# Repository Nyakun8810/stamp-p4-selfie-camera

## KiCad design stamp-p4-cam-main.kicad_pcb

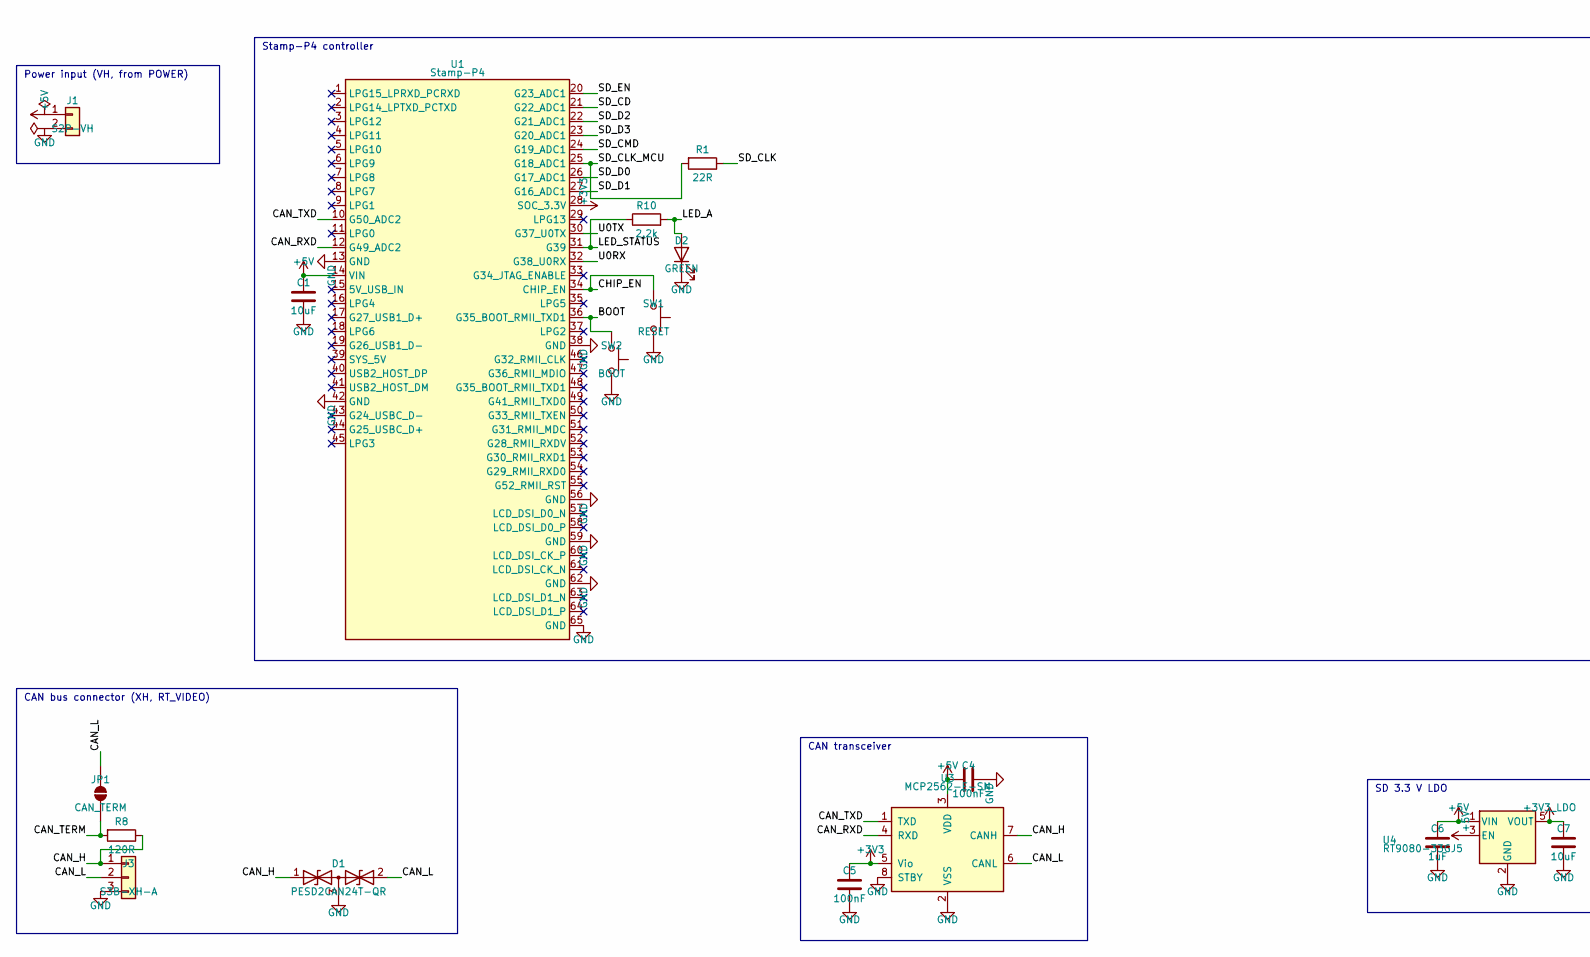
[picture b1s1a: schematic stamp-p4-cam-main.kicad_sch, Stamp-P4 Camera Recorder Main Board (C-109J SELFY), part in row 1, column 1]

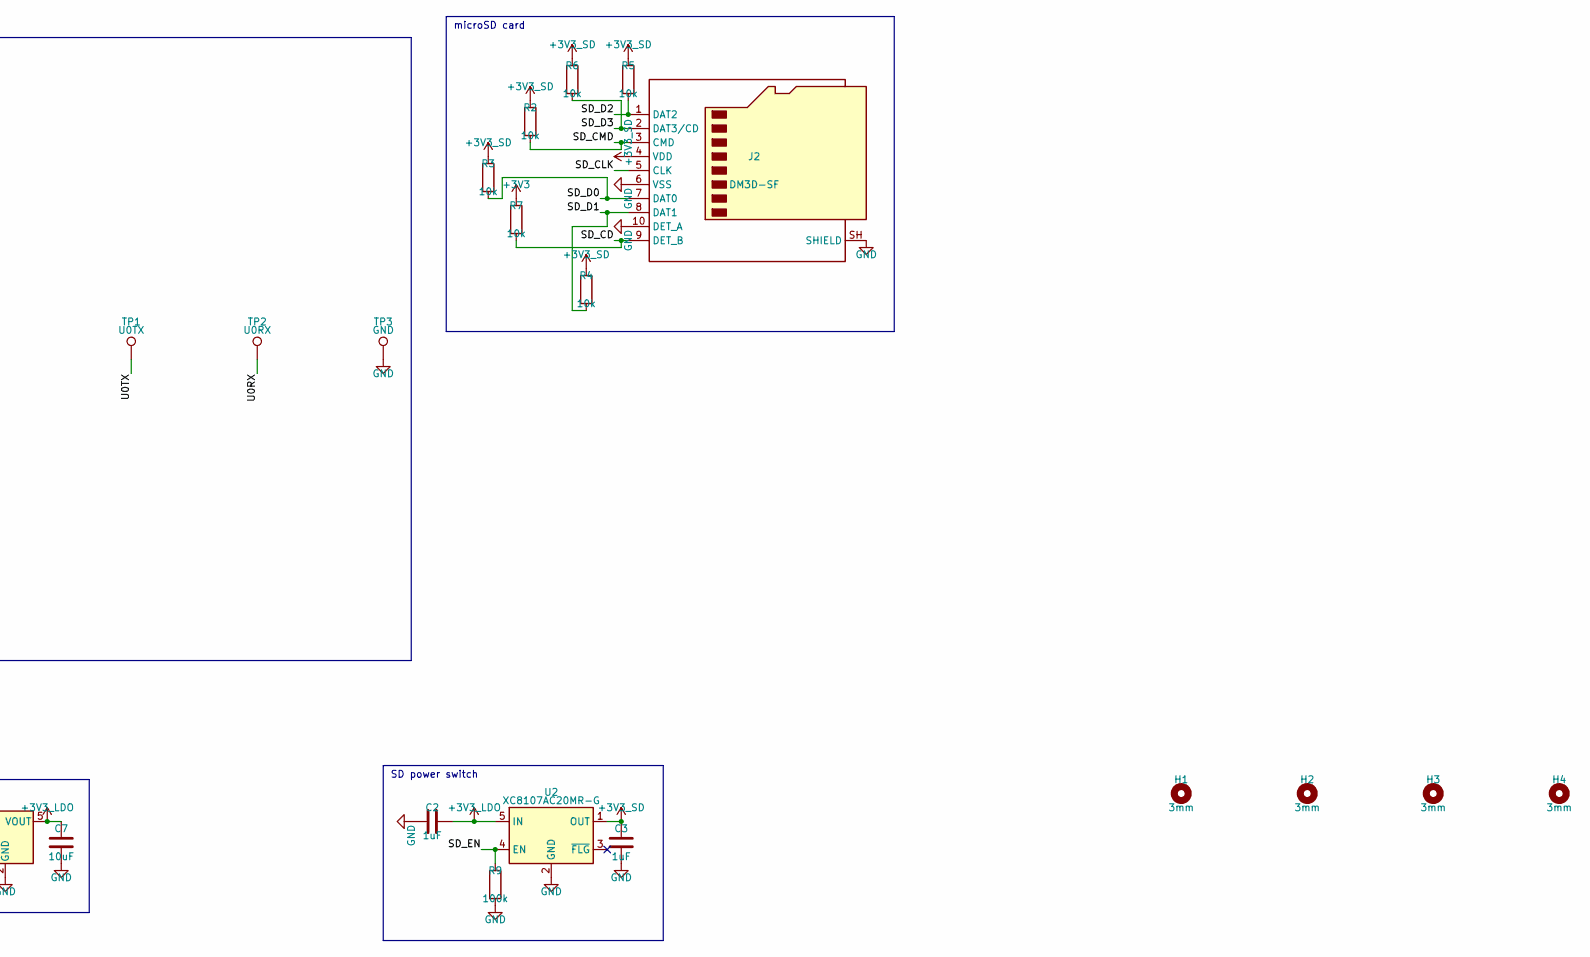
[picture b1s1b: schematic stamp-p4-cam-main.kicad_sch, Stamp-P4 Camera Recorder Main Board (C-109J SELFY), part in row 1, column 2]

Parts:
C1, C7: 10uF; C_0603_1608Metric
C2, C3, C6: 1uF; C_0402_1005Metric
C4, C5: 100nF; C_0402_1005Metric
D1: PESD2CAN24T-QR; SOT-23; MPN PESD2CAN24T-QR
D2: GREEN; LED_0603_1608Metric
H1, H2, H3, H4: 3mm; MountingHole_3mm
J1: S2P-VH; JST_VH_S2P-VH_1x02_P3.96mm_Horizontal; MPN S2P-VH
J2: DM3D-SF; microSD_HC_Hirose_DM3D-SF; MPN DM3D-SF
J3: S3B-XH-A; JST_XH_S3B-XH-A_1x03_P2.50mm_Horizontal; MPN S3B-XH-A
JP1: CAN_TERM; SolderJumper-2_P1.3mm_Open_RoundedPad1.0x1.5mm
R1: 22R; R_0402_1005Metric
R2, R3, R4, R5, R6, R7: 10k; R_0402_1005Metric
R8: 120R; R_0603_1608Metric
R9: 100k; R_0402_1005Metric
R10: 2.2k; R_0402_1005Metric
SW1: RESET; SW_SPST_B3U-1000P
SW2: BOOT; SW_SPST_B3U-1000P
TP1: U0TX; TestPoint_Pad_D1.0mm
TP2: U0RX; TestPoint_Pad_D1.0mm
TP3: GND; TestPoint_Pad_D1.0mm
U1: Stamp-P4; MPN S013
U2: XC8107AC20MR-G; SOT-23-5; MPN XC8107AC20MR-G
U3: MCP2562-E-SN; SOIC-8_3.9x4.9mm_P1.27mm; MPN MCP2562-E-SN
U4: RT9080-33GJ5; SOT-23-5; MPN RT9080-33GJ5

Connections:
+3V3: C5.1, R7.1, U1.28 (SOC_3.3V), U3.5 (Vio)
+3V3_LDO: C2.1, C7.1, U2.5 (IN), U4.5 (VOUT)
+3V3_SD: C3.1, J2.4 (VDD), R2.1, R3.1, R4.1, R5.1, R6.1, U2.1 (OUT)
+5V: C1.1, C4.1, C6.1, J1.1, U1.14 (VIN), U3.3 (VDD), U4.1 (VIN), U4.3 (EN)
/BOOT: SW2.1, U1.36 (G35_BOOT_RMII_TXD1)
/CAN_H: D1.1 (A1), J3.1, R8.1, U3.7 (CANH)
/CAN_L: D1.2 (A2), J3.2, JP1.2 (B), U3.6 (CANL)
/CAN_RXD: U1.12 (G49_ADC2), U3.4 (RXD)
/CAN_TERM: JP1.1 (A), R8.2
/CAN_TXD: U1.10 (G50_ADC2), U3.1 (TXD)
/CHIP_EN: SW1.1, U1.34 (CHIP_EN)
/LED_A: D2.2 (A), R10.2
/LED_STATUS: R10.1, U1.31 (G39)
/SD_CD: J2.9 (DET_B), R7.2, U1.21 (G22_ADC1)
/SD_CLK: J2.5 (CLK), R1.1
/SD_CLK_MCU: R1.2, U1.25 (G18_ADC1)
/SD_CMD: J2.3 (CMD), R2.2, U1.24 (G19_ADC1)
/SD_D0: J2.7 (DAT0), R3.2, U1.26 (G17_ADC1)
/SD_D1: J2.8 (DAT1), R4.2, U1.27 (G16_ADC1)
/SD_D2: J2.1 (DAT2), R5.2, U1.22 (G21_ADC1)
/SD_D3: J2.2 (DAT3/CD), R6.2, U1.23 (G20_ADC1)
/SD_EN: R9.1, U1.20 (G23_ADC1), U2.4 (EN)
/U0RX: TP2.1 (1_1), U1.32 (G38_U0RX)
/U0TX: TP1.1 (1_1), U1.30 (G37_U0TX)
GND: C1.2, C2.2, C3.2, C4.2, C5.2, C6.2, C7.2, D1.3 (common), D2.1 (K), J1.2, J2.6 (VSS), J2.10 (DET_A), J2.SH (SHIELD), J3.3, R9.2, SW1.2, SW2.2, TP3.1 (1_1), U1.13 (GND), U1.38 (GND), U1.42 (GND), U1.56 (GND), U1.59 (GND), U1.62 (GND), U1.65 (GND), U2.2 (GND), U3.2 (VSS), U3.8 (STBY), U4.2 (GND)

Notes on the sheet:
Power input (VH, from POWER)
microSD card
CAN bus connector (XH, RT_VIDEO)
Stamp-P4 controller
SD power switch
CAN transceiver
SD 3.3 V LDO

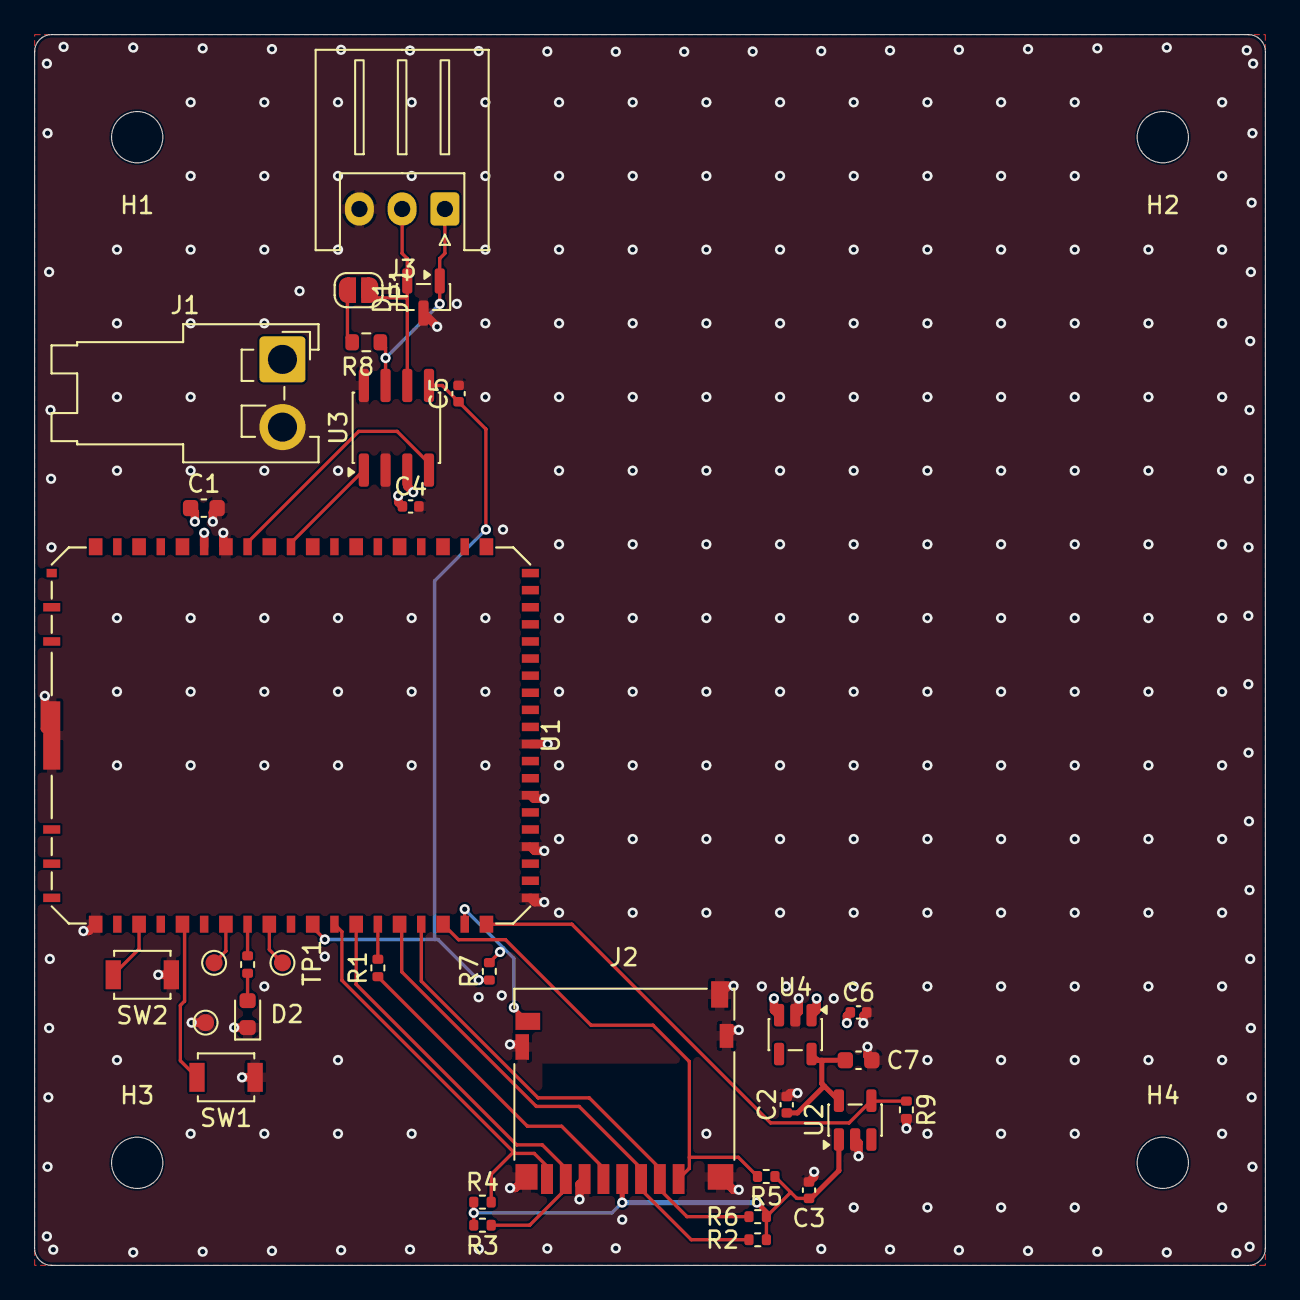
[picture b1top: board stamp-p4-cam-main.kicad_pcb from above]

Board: 4 copper layers, 72.0 x 72.0 mm, 36 parts (0 on the bottom side), 25 nets.
